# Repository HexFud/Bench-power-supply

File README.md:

# Bench-power-supply

I designed a simple and cost effective bench power supply for everyone.
To simplify the assmebly process i designed in kicad a small pcb where you connect external components

## Specifications
* IN Voltage: 24V DC
* Power Module: compatible with buck modules CC/CV based on XL4015 (5A) or XL4016 (8A)

## Included Protections
* 6.3A fusible
* schottky diode to protect against invers polarity
* filtering capacitor

## First power-up

1. Do not plug the Nano, the DPS and the displays yet.
2. Power the PCB with 24V and check the 12V rail after the LM2596 and the 3V3 rail.
3. Power off, plug everything in, and power on again with no load on the output.
4. The output stays OFF at boot; enable it with a long press on the voltage encoder.

## Firmware

* Arduino IDE, board "Arduino Nano ESP32"
* Libraries: Adafruit SSD1306, Adafruit GFX Library
* Firmware: `Firmware/bench_psu.ino`
* Register addresses and scales are constants at the top of the sketch: check them against
  the protocol document of your DPS module.

## ⚠️ Crucial Assembly Notes

1. **Modifying the Buck Converter:** 
   To mount the voltage and current controls on the front panel, you must physically desolder the original tiny blue trimmers from the purchased Buck module. Solder wires into those remaining through-holes and route them to your front-panel potentiometers.
2. **Display Wiring (CRITICAL - DO NOT BURN YOUR DISPLAY):** 
   When using the standard 5-wire Chinese dual meters (3 thin wires, 2 thick wires), **THE THIN BLACK WIRE MUST BE LEFT UNCONNECTED**. The meter derives its ground reference entirely through the thick black wire. Connecting both black wires creates a ground loop that will melt the thin wire instantly under load. (Connector `J8` on this PCB is purposely designed with only 3 pins for the thin wires).
3. **High-Current Traces:** 
   The PCB tracks handling the 24V input, the Buck module, and the outputs carry up to 5–8A. When routing the PCB, ensure power traces are made very wide (min. 2mm–3mm) or left exposed so you can reinforce them with solder.

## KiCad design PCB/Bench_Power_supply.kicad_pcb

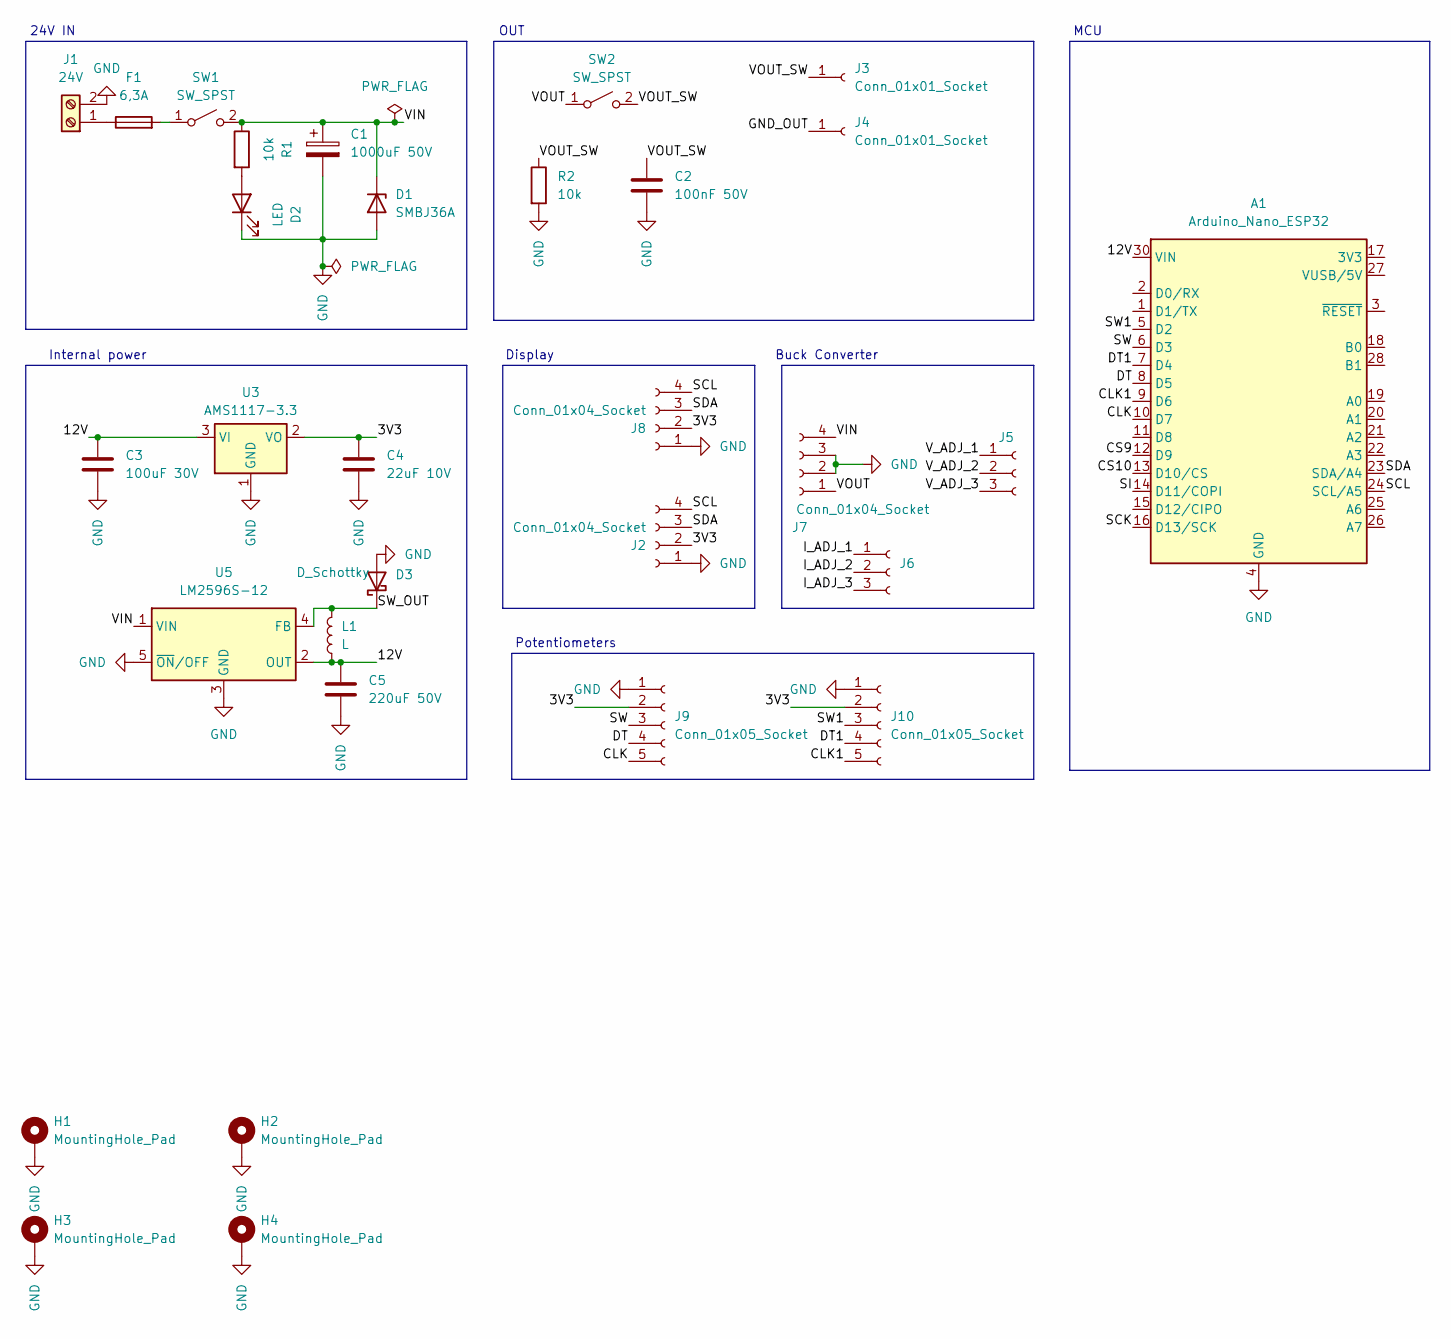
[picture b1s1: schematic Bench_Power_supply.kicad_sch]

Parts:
A1: Arduino_Nano_ESP32; Arduino_Nano
C1: 1000uF 50V; CP_Radial_D12.5mm_P5.00mm
C2: 100nF 50V; C_0805_2012Metric
C3: 100uF 30V; CP_Radial_D6.3mm_P2.50mm
C4: 22uF 10V; C_0805_2012Metric
C5: 220uF 50V; CP_Radial_D8.0mm_P3.50mm
D1: SMBJ36A; D_SMB
D2: LED; LED_0805_2012Metric
D3: D_Schottky; D_SMA
F1: 6,3A; Fuseholder_Cylinder-5x20mm_Bulgin_FX0457_Horizontal_Closed
H1, H2, H3, H4: MountingHole_Pad; MountingHole_3.2mm_M3_DIN965_Pad
J1: 24V; TerminalBlock_Phoenix_MKDS-1,5-2-5.08_1x02_P5.08mm_Horizont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
J2, J8: Conn_01x04_Socket; PinSocket_1x04_P2.54mm_Vertical
J3, J4: Conn_01x01_Socket; TestPoint_Pad_D3.0mm
J5, J6: Conn_01x03_Socket; PinHeader_1x03_P2.54mm_Vertical
J7: Conn_01x04_Socket; TerminalBlock_Phoenix_MKDS-1,5-4-5.08_1x04_P5.08mm_Horizont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
J9, J10: Conn_01x05_Socket; PinSocket_1x05_P2.54mm_Vertical
L1: L; L_Bourns_SRR1260
R1, R2: 10k; R_0805_2012Metric
SW1, SW2: SW_SPST; TerminalBlock_Phoenix_MKDS-1,5-2-5.08_1x02_P5.08mm_Horizont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
U3: AMS1117-3.3; SOT-223-3_TabPin2
U5: LM2596S-12; TO-263-5_TabPin3

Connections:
/3V3: C4.1, J2.2, J8.2, J9.2, J10.2, U3.2 (VO)
/12V: A1.30 (VIN), C3.1, C5.1, L1.1, U3.3 (VI), U5.2 (OUT)
/CLK: A1.10 (D7), J9.5
/CLK1: A1.9 (D6), J10.5
/CS9: A1.12 (D9)
/CS10: A1.13 (D10/CS)
/DT: A1.8 (D5), J9.4
/DT1: A1.7 (D4), J10.4
/GND_OUT: J4.1 (Pin_1_1)
/I_ADJ_1: J6.1
/I_ADJ_2: J6.2
/I_ADJ_3: J6.3
/SCK: A1.16 (D13/SCK)
/SCL: A1.24 (SCL/A5), J2.4, J8.4
/SDA: A1.23 (SDA/A4), J2.3, J8.3
/SI: A1.14 (D11/COPI)
/SW: A1.6 (D3), J9.3
/SW1: A1.5 (D2), J10.3
/SW_OUT: D3.1 (K), L1.2, U5.4 (FB)
/VIN: C1.1, D1.1 (K), J7.4, R1.1, SW1.2 (B), U5.1 (VIN)
/VOUT: J7.1, SW2.1 (A)
/VOUT_SW: C2.1, J3.1 (Pin_1_1), R2.1, SW2.2 (B)
/V_ADJ_1: J5.1
/V_ADJ_2: J5.2
/V_ADJ_3: J5.3
GND: A1.4 (GND), A1.29 (GND), C1.2, C2.2, C3.2, C4.2, C5.2, D1.2 (A), D2.1 (K), D3.2 (A), H1.1 (1_1), H2.1 (1_1), H3.1 (1_1), H4.1 (1_1), J1.2, J2.1, J7.2, J7.3, J8.1, J9.1, J10.1, R2.2, U3.1 (GND), U5.3 (GND), U5.5 (~ON/OFF)
unnamed: D2.2 (A), R1.2
unnamed: F1.1, J1.1
unnamed: F1.2, SW1.1 (A)

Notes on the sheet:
Internal power
Buck Converter
Display
Potentiometers
MCU
OUT
24V IN

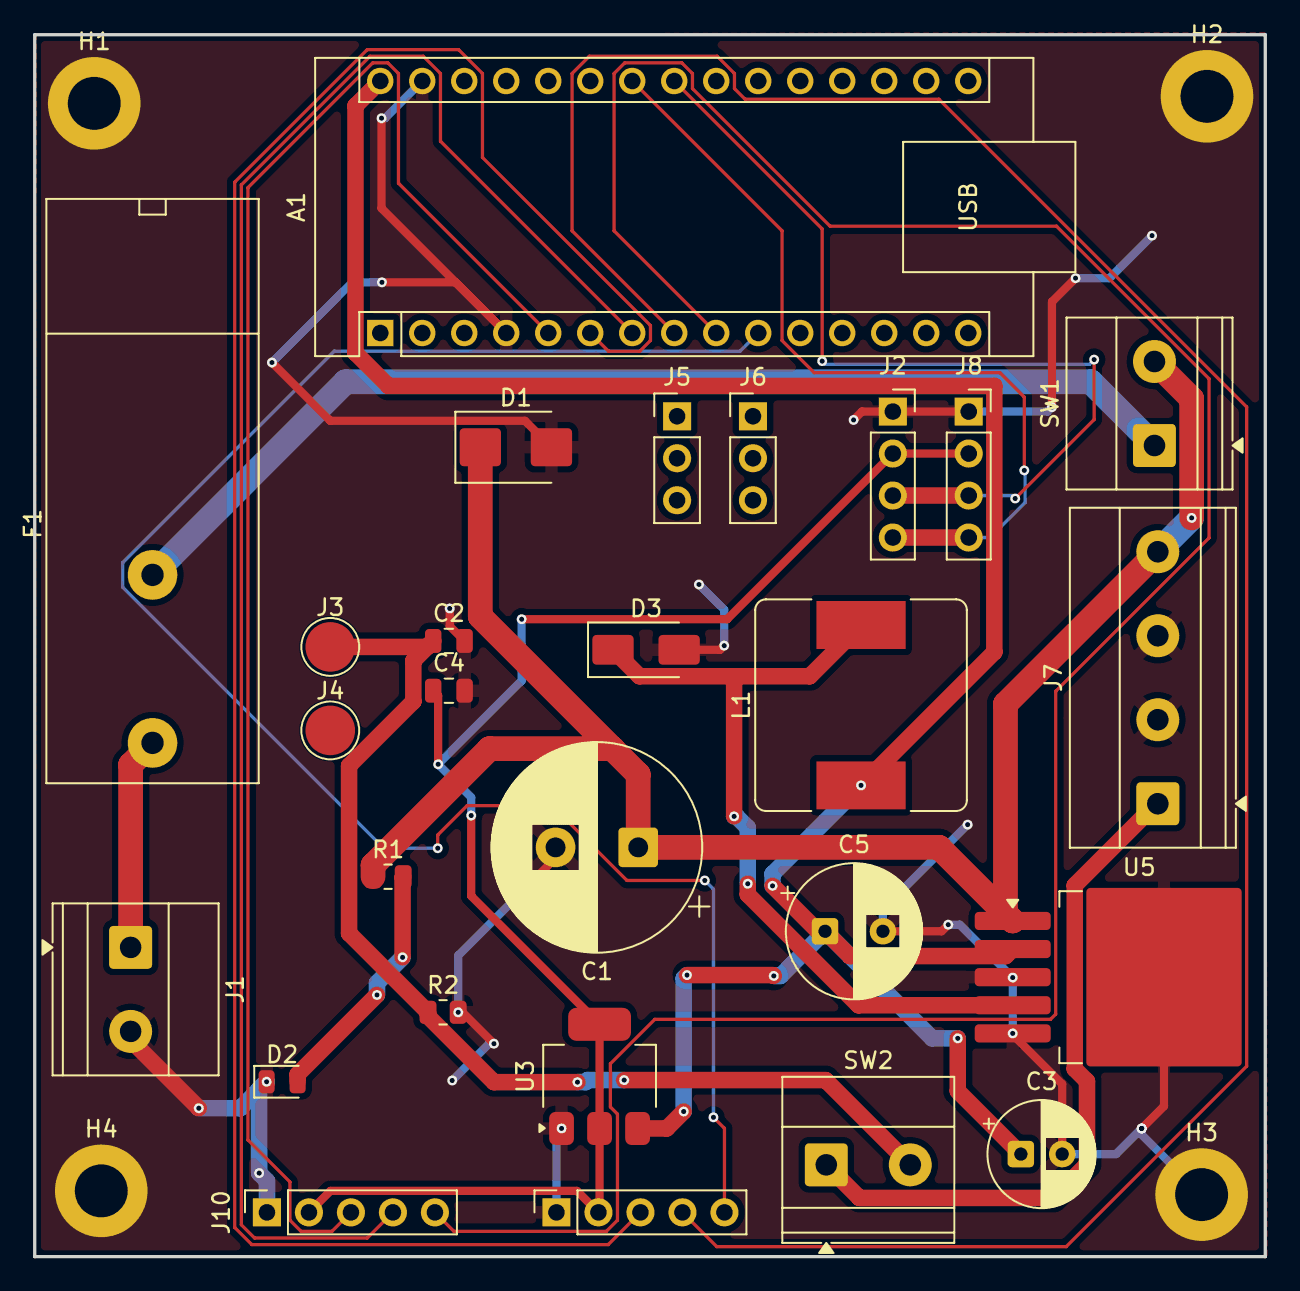
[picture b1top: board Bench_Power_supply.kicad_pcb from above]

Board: 2 copper layers, 74.4 x 73.9 mm, 31 parts (0 on the bottom side), 18 nets.

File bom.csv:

"Ref","Qty","Component","Value / Notes","KiCad Footprint","Supplier","LCSC Search Link","Est. Price USD (line total)"
"A1","1","Arduino Nano ESP32",,"Module:Arduino_Nano","Arduino Store / Mouser","https://it.aliexpress.com/item/1005009296627043.html","5"
"C1","1","Electrolytic capacitor","1000uF 50V, radial 12.5 mm","Capacitor_THT:CP_Radial_D12.5mm_P5.00mm","LCSC","https://www.lcsc.com/search?q=1000uF+50V+radial","0,82"
"C2","1","Ceramic capacitor","100nF 50V X7R, 0805","Capacitor_SMD:C_0805_2012Metric","LCSC","https://www.lcsc.com/search?q=100nF+50V+0805","0,94"
"C3","1","Electrolytic capacitor","100uF 25V, radial 6.3 mm (change symbol to C_Polarized)","Capacitor_THT:CP_Radial_D6.3mm_P2.50mm","LCSC","https://www.lcsc.com/search?q=100uF+25V+radial","0.1"
"C4","1","Tantalum capacitor","22uF 16V, case B (AMS1117 stability)","Capacitor_Tantalum_SMD:CP_EIA-3528-21_Kemet-B","LCSC","https://www.lcsc.com/search?q=22uF+16V+tantalum","0.2"
"C5","1","Low-ESR electrolytic capacitor","220uF 25V or higher, radial 8 mm (change symbol to C_Polarized)","Capacitor_THT:CP_Radial_D8.0mm_P3.50mm","LCSC","https://www.lcsc.com/search?q=220uF+25V+low+ESR","0.3"
"D1","1","SMBJ36A unidirectional TVS","Not the CA version (bidirectional)","Diode_SMD:D_SMB","LCSC","https://www.lcsc.com/search?q=SMBJ36A","0.50"
"D2","1","LED 0805","Power indicator","LED_SMD:LED_0805_2012Metric","LCSC","https://www.lcsc.com/search?q=LED+0805","0.03"
"D3","1","SS36 Schottky diode","3A 60V, SMA","Diode_SMD:D_SMA","LCSC","https://www.lcsc.com/search?q=SS36","0.15"
"F1","1","6.3A 5x20 fuse + fuse holder","Pick the holder first, then adapt the footprint","Fuse:Fuseholder_Cylinder-5x20mm_Bulgin_FX0457_Horizontal_Closed","LCSC","https://www.lcsc.com/search?q=5x20+fuse+holder+PCB","1.0"
"J1","1","2-pin screw terminal","5.08 mm, 24V input","TerminalBlock_Phoenix:TerminalBlock_Phoenix_MKDS-1,5-2-5.08_1x02_P5.08mm_Horizontal","LCSC","https://www.lcsc.com/search?q=5.08mm+screw+terminal+2P","0.5"
"J7","1","4-pin screw terminal","5.08 mm, to the DPS module","TerminalBlock_Phoenix:TerminalBlock_Phoenix_MKDS-1,5-4-5.08_1x04_P5.08mm_Horizontal","LCSC","https://www.lcsc.com/search?q=5.08mm+screw+terminal+4P","0.8"
"J2, J8","2","1x4 female header","I2C displays (GND, 3V3, SDA, SCL): check the pin order of your modules","Connector_PinSocket_2.54mm:PinSocket_1x04_P2.54mm_Vertical","LCSC","https://www.lcsc.com/search?q=female+header+1x4+2.54","0.3"
"J9, J10","2","1x5 female header","Encoders (GND, 3V3, SW, DT, CLK)","Connector_PinSocket_2.54mm:PinSocket_1x05_P2.54mm_Vertical","LCSC","https://www.lcsc.com/search?q=female+header+1x5+2.54","0.3"
"J5","1","1x3 female header","Serial to DPS (TX, RX, GND); delete J6","Connector_PinSocket_2.54mm:PinSocket_1x03_P2.54mm_Vertical","LCSC","https://www.lcsc.com/search?q=female+header+1x3+2.54","0.2"
"L1","1","Power inductor","47uH, at least 3.5A (e.g. SRR1260 series); check the LM2596 datasheet nomograph","Inductor_SMD:L_Bourns_SRR1260","LCSC","https://www.lcsc.com/search?q=SRR1260-470M","1.50"
"R1, R2","2","10k resistor","0805","Resistor_SMD:R_0805_2012Metric","LCSC","https://www.lcsc.com/search?q=10k+0805","0.04"
"U3","1","AMS1117-3.3 regulator","SOT-223 (fed from the 12V rail)","Package_TO_SOT_SMD:SOT-223-3_TabPin2","LCSC","https://www.lcsc.com/search?q=AMS1117-3.3","0.2"
"U5","1","LM2596S-12 regulator","TO-263-5","Package_TO_SOT_SMD:TO-263-5_TabPin3","LCSC","https://www.lcsc.com/search?q=LM2596S-12","1.5"
"-","1","Riden DPS5005 communication version","Programmable buck 0-50V 5A, 6-55V input, Modbus serial. With a 24V input the output tops out around 23V","-","AliExpress / Amazon / Riden resellers","https://it.aliexpress.com/item/1005003611553445.html","30"
"SW1, SW2","2","SPST switch 10A DC","Rated for DC current","(external, on terminals)","Amazon / AliExpress","https://it.aliexpress.com/item/1005005261096988.html","4.0"
"-","2","0.96 inch I2C OLED display","Check pin order (GND, VCC, SCL, SDA)","(external)","Amazon / AliExpress","https://it.aliexpress.com/item/1005006141235306.html","6.0"
"-","2","KY-040 encoder module","Correct pin-to-pin cable to J9/J10","(external)","Amazon / AliExpress","https://it.aliexpress.com/item/1005006060621481.html","3.0"
"-","2","Encoder knob","May be included with encoder purchase","(external)","Amazon / AliExpress",,"2.0"
"-","1","Banana binding post pair (red and black)","Rated for 5A","(external)","Amazon / AliExpress","https://it.aliexpress.com/item/1005005610222281.html","4.0"
"-","1","24V DC power supply","At least 5A","(external)","Amazon / AliExpress","https://www.amazon.it/Security-01-Alimentatore-spina-Plug-XH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","13"
"-","1","Custom PCB (batch of 5-10)","Fabrication + shipping","(Gerber files)","JLCPCB or similar",,"20"
"-","1","2-channel oscilloscope","for ripple and noise analysis","(external)","Amazon / AliExpress","https://it.aliexpress.com/item/1005009751654965.html","160.0"
TOTAL,,,,,,,254
